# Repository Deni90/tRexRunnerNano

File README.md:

# Welcome to tRexRunnerNano Project

## About
This project tries to be the smallest implementation of Google's easter egg T-Rex Runner with resolution of only 128x32px.

The goal is to make a small game console by using WCH CH32V003 microcontroller and SSSD1306 oled display.

## Schematic  & PCB
Made with KiCAD 10

## Firmware

Firmware is written in C using **ch32fun**, an open source development environment for the CH32V003.

WCH CH-Link is used for flashing the firmware

### Building and flashing

```
make
```

## DM DIY-MORE OLED-091
Popular I2C OLED 32x128 display from diy-more has an issue. It doesn't properly start after power on, but starts without problems after reset.
To solve this problem swap R3 and R4 resistors.

Solution found at:
https://youtu.be/__3InV5tdzM

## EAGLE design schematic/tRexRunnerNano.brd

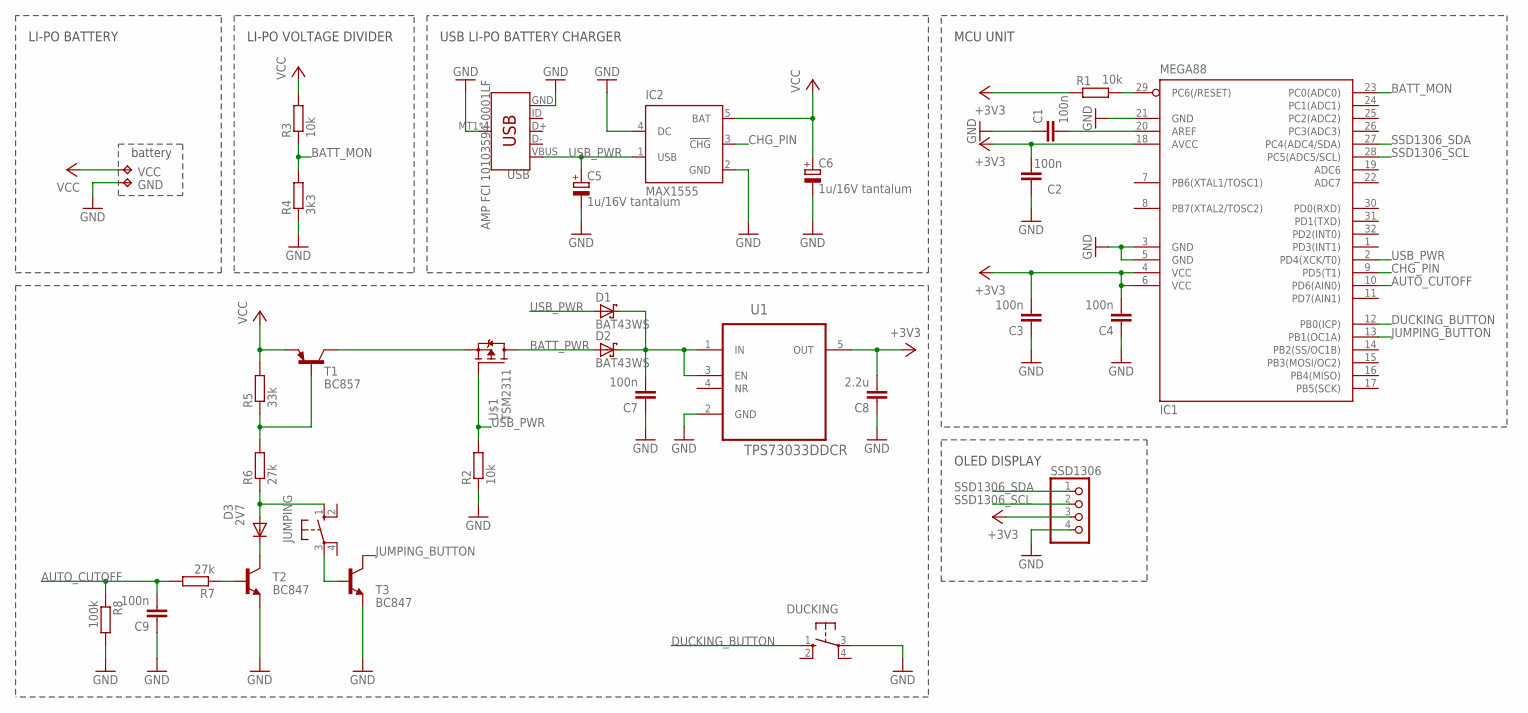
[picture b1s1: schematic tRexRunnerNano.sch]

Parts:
C1, C2, C3, C4, C7, C9: 100n; C0805
C5, C6: 1u/16V tantalum; SMC_A
C8: 2.2u; C0805
D1, D2: BAT43WS; SOD323_ST
D3: 2V7; SOD80C
DUCKING: 10-XX; B3F-10XX
GND: TPTP12R; TP12R
IC1: MEGA88; TQFP32-08
IC2: MAX1555; SOT23-5L
JUMPING: 10-XX; B3F-10XX
R1, R2, R3: 10k; R0805
R4: 3k3; R0805
R5: 33k; R0805
R6, R7: 27k; R0805
R8: 100k; R0805
SSD1306: PINHD-1X4; 1X04
T1: BC857; SOT23-BEC
T2, T3: BC847; SOT23
U1: TPS73033DDCR; SOT95P290X145-5N
U$1: TSM2311; SOT23
USB: AMP FCI 10103594-0001LF; USB-MICROB
VCC: TPTP12R; TP12R

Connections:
+3V3: C2.2, C3.2, C4.2, C8.2, IC1.4 (VCC), IC1.6 (VCC), IC1.18 (AVCC), R1.1, SSD1306.3, U1.5 (OUT)
AUTO_CUTOFF: C9.2, IC1.10 (PD6(AIN0)), R7.2, R8.1
BATT_MON: IC1.23 (PC0(ADC0)), R3.1, R4.2
BATT_PWR: D2.A, U$1.3 (D)
CHG_PIN: IC1.9 (PD5(T1)), IC2.3 (!CHG)
DUCKING_BUTTON: DUCKING.1 (S), IC1.12 (PB0(ICP))
GND: C1.1, C2.1, C3.1, C4.1, C5.-, C6.-, C7.1, C8.1, C9.1, DUCKING.3, GND.TP, IC1.3 (GND), IC1.5 (GND), IC1.21 (GND), IC2.2 (GND), IC2.4 (DC), R2.1, R4.1, R8.2, SSD1306.4, T2.2 (E), T3.2 (E), U1.2 (GND), USB.GND, USB.MT1 (SHIELD), USB.MT2 (SHIELD), USB.P$1 (SHIELD), USB.P$2 (SHIELD)
JUMPING_BUTTON: IC1.13 (PB1(OC1A)), T3.3 (C)
unnamed: IC1.29 (PC6(/RESET)), R1.2
unnamed: C1.2, IC1.20 (AREF)
unnamed: T1.C, U$1.2 (S)
unnamed: C7.2, D1.C, D2.C, U1.1 (IN), U1.3 (EN)
unnamed: R7.1, T2.1 (B)
unnamed: R5.1, R6.2, T1.B
unnamed: D3.A, JUMPING.1 (S), R6.1
unnamed: D3.C, T2.3 (C)
unnamed: JUMPING.3, T3.1 (B)
SSD1306_SCL: IC1.28 (PC5(ADC5/SCL)), SSD1306.2
SSD1306_SDA: IC1.27 (PC4(ADC4/SDA)), SSD1306.1
USB_PWR: C5.+, D1.A, IC1.2 (PD4(XCK/T0)), IC2.1 (USB), R2.2, U$1.1 (G), USB.VBUS
VCC: C6.+, IC2.5 (BAT), R3.2, R5.2, T1.E, VCC.TP

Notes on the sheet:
MCU UNIT
USB LI-PO BATTERY CHARGER
battery
OLED DISPLAY
LI-PO VOLTAGE DIVIDER
LI-PO BATTERY

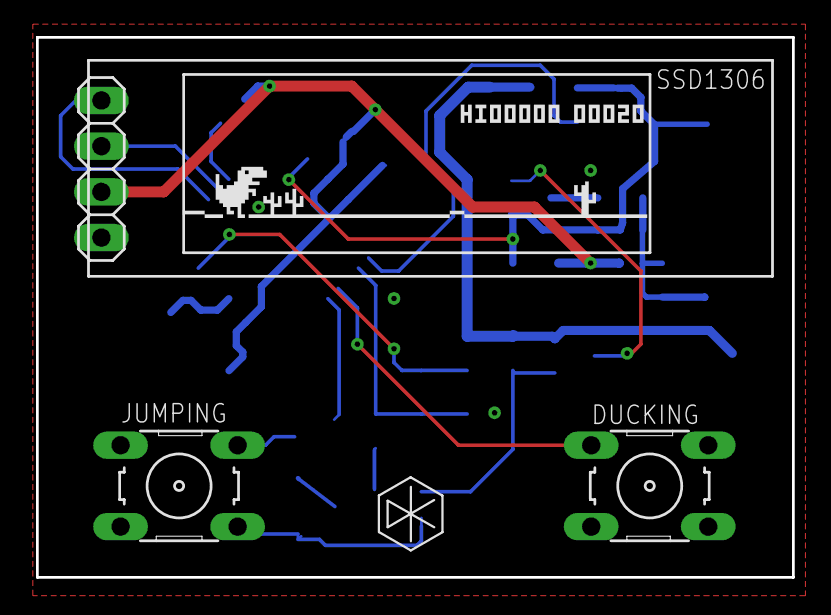
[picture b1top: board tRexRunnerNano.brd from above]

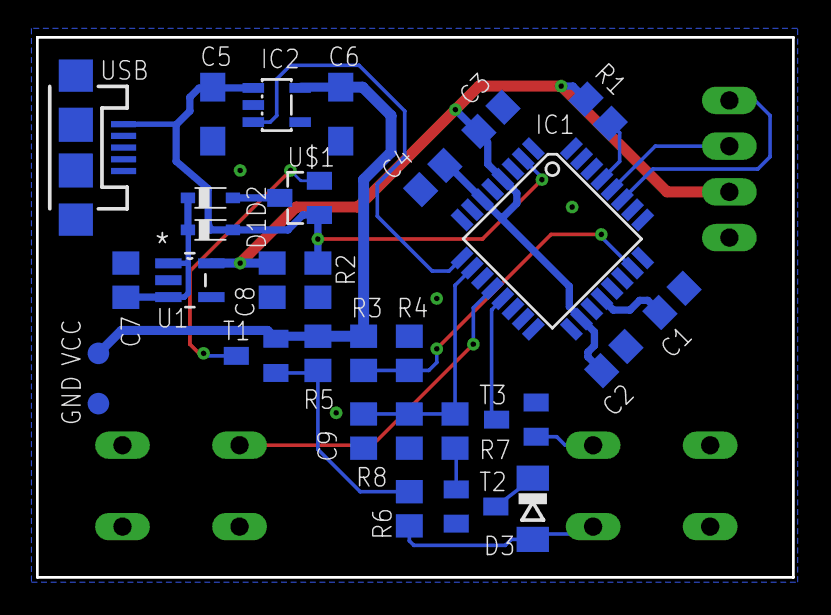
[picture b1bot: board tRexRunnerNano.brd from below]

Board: 2 copper layers, 42.0 x 30.0 mm, 33 parts (30 on the bottom side), 21 nets.

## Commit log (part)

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2018-07-16 Initializes timer.
2018-07-16 Adds game objects and animations
    - trex animations (running, jumping, ducking)
    - horizon movement
    - flying pterodactyl
    - cactus obstacles
2018-07-17 Adds button handling and miror changes
    - handles buttons
    - updates trex state based on buttons activity
    - changes game parameters
    - adds FB_drawGameObject function
2018-07-17 Fixes formatting game_object definitions
2018-07-18 Adds TODOs
2018-07-18 Refactors button handling
    - button io initialization moved to function
    - created button state monitor
2018-07-18 Moves horizon part to a function
2018-07-18 Moves pterodactyl stuff into function
2018-07-18 Moves trex animations into separate functions
2018-07-18 Adds cactus handling
2018-07-18 Adds cactus and pterodactyl creation
    - extended game_object_t with 'delta'
    - added PNRG initialization
2018-07-19 Adds creation of one more cactus type
2018-07-19 Implements random cactus generation.
2018-07-19 Implements periodic update of game speed
2018-07-23 Renamed FB_functions, replaces button pins with macros
2018-07-23 Implements random pterodactyl generation.
2018-07-23 Implements score and high score.
2018-07-23 Adds clearance between new horizon and trex.
2018-07-23 Adjust game parameters.
2018-07-30 Replaces cactus3 with different design.
2018-07-30 Fixes trex ducking glitch.
2018-07-30 Moves defines with dimensions to source file.
2018-07-31 Fixes dead trex sprite and minor changes.
2018-08-02 Refactoring
    - merges cactuses and pterodactyl into obstacles
    - changes game_objects update functions
    - fixes initialization of cactuses
2018-08-02 Moves sprites into separate header file
2018-08-02 Reimplements horizon drawing
    - creates horizon_t structure
2018-08-02 Implements collision detection
2018-08-02 Implements re(starting) of the game.
    - variables from main() are now global
    - refactored GAME_ funtions
2018-08-02 Tunes game parameters, updates Makefile
    - frame rate dropped to 50FPS
    - MCU frequency set to 8MHz
    - updated MCU fuse bits
2018-08-02 Fixes trex crash into horizon during landing.
2018-08-03 Updates GAME_init and tunes game parameters
    game_speed and trex_state added to GAME_init
2018-08-06 Removes deltas from game_object_t and horizon_t
2018-08-06 Reimplements obstacle generation.
2018-08-06 Changes pterodactyl flying heights.
2018-08-06 Game tuning
2018-08-06 Shows "game over" splash.
2018-08-06 Removes debug print.
2018-08-09 Create LICENSE
2018-08-09 Introduces inverted color mode.
2018-08-09 Fixes trexs jumping height, moves score 1px down.
2018-08-09 Makes variable for avr programmer in Makefile.
2018-08-09 Creates README file
    - adds image folder
2018-09-04 Adds initial hardware desing.
2018-09-05 Changes via sizes.
2018-10-10 Code refactoring by moving it info functions.
    - GAME_AdjustDifficulty: increasing game speed and distance between obstacles
    - GAME_HandleState: switching trex states based on button presses
2018-10-10 Implemented storing high score in eeprom.
2018-10-10 Adds power manager and initializes io pins.
2018-11-19 Fixes read/write from/to eeprom.
2018-11-19 Implements inactivity monitor.
2018-11-19 Implements battery monitoring.
2018-11-20 No need for delay at startup.
    Check README for the solution.
2018-11-20 Removes trex_dead sprite and WAITING state.
2018-11-21 Implements the startup of the device.
    To start the device both buttons should be held for STARTUP_INTERVAL.
    - new function FB_DrawRectangle
    - deleted unused TIMER_delay
2018-11-21 Removes unused functions and refactores code.
    - removed FB_ClearPixel
    - POWER_MANAGER_turnOn and POWER_MANAGER_turnOff converted to macros
    - removed GAME_BackupHighScore and GAME_RestoreHighScore
2018-11-21 Fixes trex jumping height.
2019-01-08 Fixes typo and POWER_MANAGER_ReadBatteryVoltage
2019-01-08 Implement power management (usb & battery charging)
    - created POWER_MANAGER_ShowBatteryStatus for showing battery icon
    - added checking for low battery
    - fixed intialization of CHG_PIN
    - declared TIMER, BUTTON and POWER_MANAGER functions in the header
2019-01-08 Small adjustments of OLED and USB connectors
    - OLED connector has been moved 1mm left
    - micro USB connector has been moved 1mm right
2019-01-08 Schematic: Changes D3 to 2V7
2019-01-16 Decreases gravity to 3.1
2019-01-16 Fixes the horizon when trex is jumping.
2019-01-17 Board: Repositions oled connector, usb and buttons
2019-03-12 Fixes turning off when the init isn't successful
2019-03-12 Fixes Timer1's TOP value for 1mS
2019-03-12 Tunes game parameters and timeout at init.
2019-04-27 Tunes timeout and score inclement values.
2019-04-27 Adds watchdog timer.
2019-04-27 Fixes early start of the game at startup.
2019-04-27 Repositions ssd1306 text on PCB
2019-04-29 Reimplements: Fix for early start of the game at startup.
    - no need for using timer
2019-04-29 Makefile: renames flash_eeprom target to eeprom.
    - updates README file
2019-05-05 Prevents immediate start of the game after gameover
2019-06-25 Implements reseting high score.
2019-06-26 Fizes oled burn while charging battery.
2019-06-26 Fixes bugs when turning off the device.
2019-07-14 Enables BOD at VCC=2V7.
2019-09-16 Enables EESAVE fuse bit to preserve eeprom.
2022-02-06 Adds 3D model for casing
2024-12-17 Port tRexRunner to rpi Pico 2W
2026-05-20 Initial port of firmware to CH32 with new PCB
2026-05-20 Reorganize code
    - Move macros, type definitions, forward declarations to the source file.
    - Make functions static
2026-05-20 Rename button names to match with schematic
2026-05-20 Port POWER_MANAGER to the project
    - Implement ADC init and ADC read functions based on ch32fun examples
2026-05-20 Fix FLASH_Write_u32
    Use code from ch32fun/examples/flashtest/flashtest.c to fix the function
2026-05-21 Port the startup sequence of the game to this repo
2026-05-21 Fix clang-tidy warnings related to braces, types and magic numbers
2026-05-24 Refactor tRexRunner.c to make it more modular and readable.
    - Introduce a state machine representing states of the device
    - Move state implementations to separate functions to make the code more
    readable and maintainable.
    - Handle initialization and factory reset through states removing the need for
    infinite loops.
    - Re-implement BUTTONS_MonitorButtons function to use standard debouncing
2026-05-24 Remove clear function from SSD1306
2026-05-24 PCB: Move vias out out test pads
2026-05-24 Extend state machine with SYS_BATTERY_CHARGING state
    - Rename POWER_MANAGER_ShowBatteryStatus to FB_ShowBatteryStatus
    - Handle battery chargin state in SYS_ProcessBatteryCharging
    - Turn off periodic checks (like buttons, inactivity, ...) while in
    SYS_BATTERY_CHARGING state

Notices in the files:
parts and their libraries:
SparkFun-Connectors: Licensing: Creative Commons ShareAlike 4.0 International - https://creativecommons.org/licenses/by-sa/4.0
